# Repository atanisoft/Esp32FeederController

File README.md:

# Esp32FeederController

The Esp32FeederController project allows controlling of multiple 0816 Feeders
using four wire cables.

## Supported Feeders

At this time the following feeder designs should work:

* [Original 0816 Feeder](https://docs.mgrl.de/maschine:pickandplace:feeder:0816feeder).
* [0816 Lumen Feeder](https://github.com/SupaCoder/0816-Lumen-SMT-Feeder-Remix).
* [Max Feeder](https://github.com/CurlyTaleGamesLLC/MAXFeederShield).

The [Max Feeder](https://github.com/CurlyTaleGamesLLC/MAXFeederShield) is the preferred
version of the feeder design as it supports adding a QR Code to the feeder that can be
used for automatic part identification.

### Feeder modifications / Addons

* [Reel holder](https://www.thingiverse.com/thing:3810696)
* [Vertical tape puller](https://github.com/SebG3D/TapePuller/wiki)

## Non-automatic feeders

* [Lumen Push/Pull Feeder](https://github.com/GatCode/LumenPPF)

# Adding Esp32FeederController to OpenPnP

Adding Esp32FeederController to OpenPnP consists of three steps:

* Create [GcodeDriver](https://github.com/openpnp/openpnp/wiki/GcodeDriver).
* Create [Actuators](https://github.com/openpnp/openpnp/wiki/Setup-and-Calibration%3A-Actuators) for Feeder actions.
* Create [Feeders](https://github.com/openpnp/openpnp/wiki/Setup-and-Calibration%3A-Feeders). 

### Creating the Gcode Driver

Each Esp32FeederController PCB should have it's own [GcodeDriver](https://github.com/openpnp/openpnp/wiki/GcodeDriver).

Steps to add a new [GcodeDriver](https://github.com/openpnp/openpnp/wiki/GcodeDriver) for Esp32FeederController:

* Navigate to the `Machine Setup` tab
* Traverse the list to the `Drivers` section, select and expand it.
* Click the `+` (add) icon and select `GcodeDriver`.
* Select the newly created `GcodeDriver GcodeDriver` entry.
* Set the `Name` so it can be easily identified later.
* Set `Communications Type` to `tcp`.
* Scroll down to the `TCP` section.
* Set `IP Address` based on the reported IP address in the serial output.
* Set `Port` to `8989`.
* Click the `Apply` button to save the updates.
* In the `File` menu select `Save Configuration` to ensure settings are not lost when restarting OpenPnP.

### Creating Actuators

Each Esp32FeederController PCB requires two `Actuators`:

* Feeder Advancement
* Feeder Post Pick

The following steps should be executed for the two `Actuators`:

* Navigate to the `Machine Setup` tab
* Traverse the list to the `Actuators` section, select and expand it.
* Click the `+` (add) icon and select `ReferenceActuator`.
* Select the newly created `ReferenceActuator ReferenceActuator` entry.
* Set `Driver` to the Esp32FeederController driver created previously.
* Set the `Name` so it can be easily identified later.
* Set `Value Type` to `Double`.
* Click the `Apply` button to save the updates.
* In the `File` menu select `Save Configuration` to ensure settings are not lost when restarting OpenPnP.

After the two `Actuators` have been defined it is necessary to configure the
Gcode commands to send for actuation, use the following steps to configure this:

* Navigate to the `Machine Setup` tab
* Traverse the list to the `Drivers` section, select and expand it.
* Click the `GcodeDriver Esp32FeederController` (or whatever name was provided previously).
* Navigate to the `Gcode` tab.
* In `Head Mountable` drop down select `Default`.
  * In `Setting` select `COMMAND_CONFIRM_REGEX` and enter `^ok.*`, be sure to click `Apply` before moving further.
  * In `Setting` select `COMMAND_ERROR_REGEX` and enter `^error.*`, be sure to click `Apply` before moving further.
* In `Head Mountable` drop down select `Actuator: [No Head] Feeder Advancement`.
  * In `Setting` select `ACTUATE_DOUBLE_COMMAND` and enter `M610 N{IntegerValue}*`, be sure to click `Apply` before moving further.
* In `Head Mountable` drop down select `Actuator: [No Head] Feeder Post Pick`.
  * In `Setting` select `ACTUATE_DOUBLE_COMMAND` and enter `M611 N{IntegerValue}*`, be sure to click `Apply` before moving further.
* In the `File` menu select `Save Configuration` to ensure settings are not lost when restarting OpenPnP.

## Configuring Feeders in OpenPnP

There are two types of feeders that will work well with Esp32FeederController:

* [ReferenceAutoFeeder](https://github.com/openpnp/openpnp/wiki/ReferenceAutoFeeder)
* [ReferenceSlotAutoFeeder](https://github.com/openpnp/openpnp/wiki/ReferenceSlotAutoFeeder)

Both operate similarly using the `Actuators` defined above.

* Navigate to the `Feeders` tab
* Click the `+` (add) icon and select `ReferenceAutoFeeder` or `ReferenceSlotAutoFeeder`.
* Select the newly created `ReferenceAutoFeeder ReferenceAutoFeeder` or `ReferenceSlotAutoFeeder ReferenceSlotAutoFeeder` entry.
* Double click on the newly created row in the `Name` column and rename it for easier identification.
* Set `Feed Actuator` to `Feeder Advancement` (or whichever name you provide the `Actuator`)
* Set `Post Pick Actuator` to `Feeder Post Pick` (or whichever name you provide the `Actuator`)
* Set `Actuator Value` on both `Actuators` to the feeder number on the Esp32FeederController PCB minus one (zero indexed).
* Click the `Apply` button to save the updates.
* In the `File` menu select `Save Configuration` to ensure settings are not lost when restarting OpenPnP.

Use the `Test Feed` and `Test post pick` to confirm the feeder is responding correctly.

## Supported Gcode commands

The Esp32FeederController supports multiple Gcode commands, many of which are
not directly used by OpenPnP. Many of the commands are intended to be used with
substitution of values within `{ }` marks, anything within `[ ]` are optional
arguments.

### Feeder Movement (M610)

`M610 N{feeder} [D{distance}]`

* `{feeder}` is the Feeder to be moved forward.
* `{distance}` is the distance to move the feeder and is optional.

### Feeder Post Pick (M611)

`M611 N{feeder}`

* `{feeder}` is the Feeder to be moved as part of post-pick.

### Feeder Status (M612)

`M612 N{feeder}`

* `{feeder}` is the Feeder to retrieve status for.

### Feeder Configuration (M613)

`M613 N{feeder} [A{advance angle}] [B{half advance angle}] [C{retract angle}] [D{degrees}] [F{feed length}] [S{speed}] [U{settle time}] [V{min pulse}] [W{max pulse}] [Z{feedback enabled}]`

All parameters except `{feeder}` are optional.

* `{feeder}` is the Feeder to be configured.
* `{advance angle}` is the angle to move the servo to for full extension.
* `{half advance angle}` is the angle to move the servo to for half extension.
* `{retract angle}` is the angle to move the servo to for retraction.
* `{degrees}` is the maximum number of degrees to move at one time, set to zero to move immediately.
* `{feed length}` is the number of millimeters (pitch) to move the feeder forward when moving to the next part and must be a multiple of 2.
* `{speed}` is the interval at which to move the servo between two angles, used in conjunction with `{degrees}`.
* `{settle time}` is the number of milliseconds to delay between servo movements.
* `{min pulse}` is the minimum number of pulses to send the servo.
* `{max pulse}` is the maximum number of pulses to send the servo.
* `{feedback enabled}` is used to enable or disable feedback checking as part of movement, set to zero to disable or one to enable

### Enable Feeder (M614)

`M614 N{feeder}`

* `{feeder}` is the Feeder to enable.

### Disable Feeder (M615)

`M615 N{feeder}`

* `{feeder}` is the Feeder to disable.

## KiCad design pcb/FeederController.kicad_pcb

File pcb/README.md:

# Custom PCBs

This tree contains custom PCBs for the Esp32FeederController. Note that this PCB
has not been extensively tested or verified to be bug-free. Please report any
issues with the PCBs and if possible a PR to correct them.

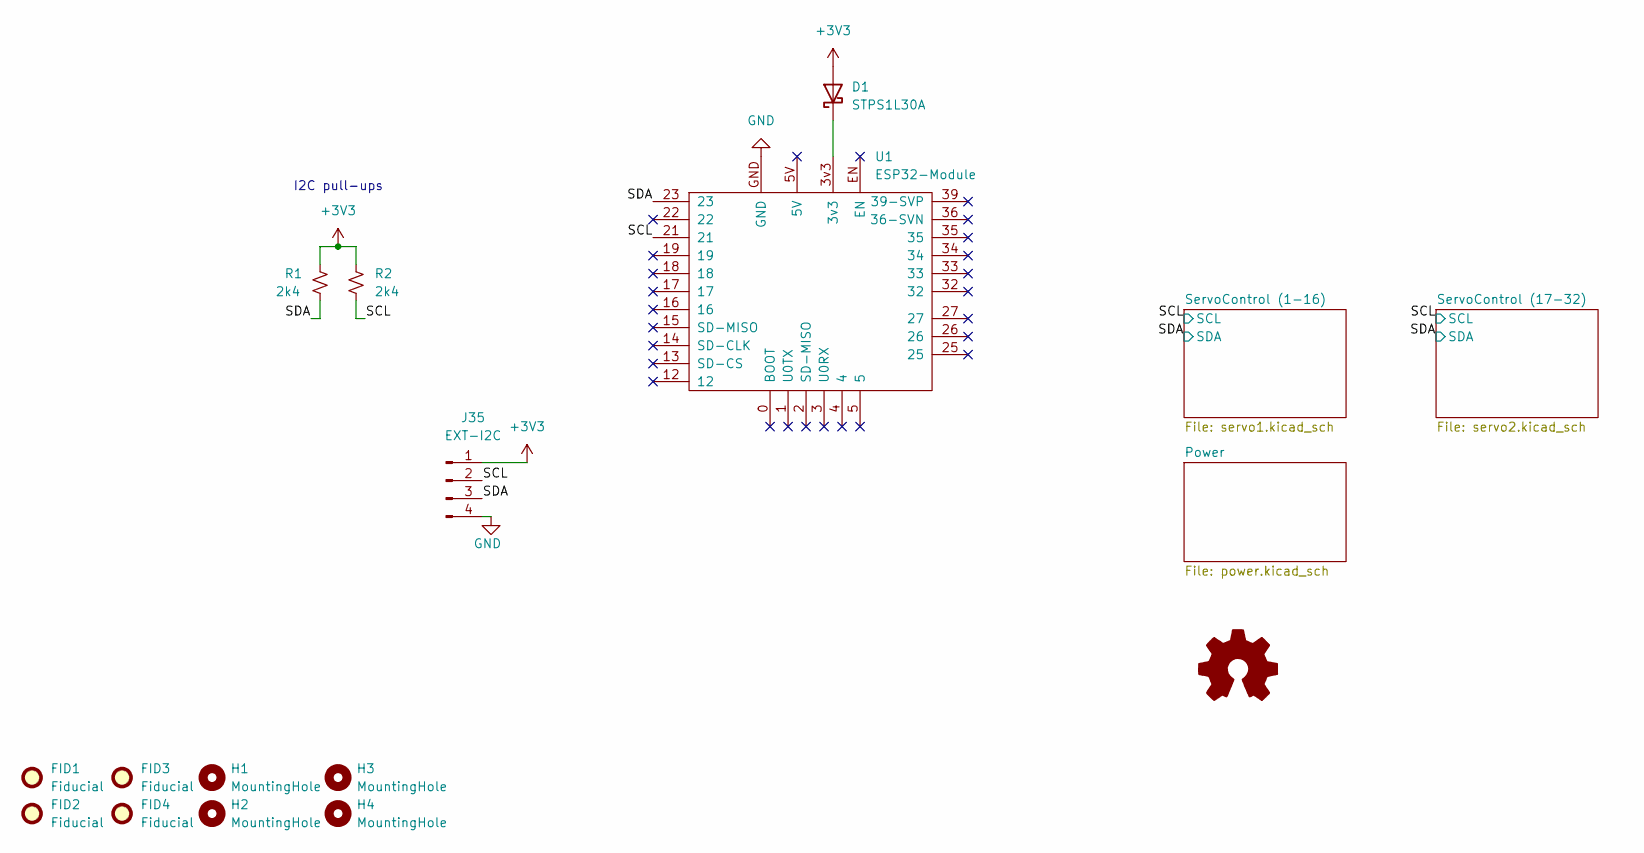
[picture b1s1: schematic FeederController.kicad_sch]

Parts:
D1: STPS1L30A; D_SMA_Handsoldering; Mouser 511-STPS1L30AFN
FID1, FID2, FID3, FID4: Fiducial; Fiducial_0.5mm_Mask1mm
H1, H2, H3, H4: MountingHole; MountingHole_3.2mm_M3_Pad
J35: EXT-I2C; PinHeader_1x04_P2.54mm_Vertical
R1, R2: 2k4; R_0603_1608Metric_Pad0.98x0.95mm_HandSolder
U1: ESP32-Module; TTGO-T1-DEVKIT-C

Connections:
+3V3: D1.2 (A), J35.1, R1.1, R2.1; also elsewhere on the board
/SCL: J35.2, R2.2, U1.21; also elsewhere on the board
/SDA: J35.3, R1.2, U1.23; also elsewhere on the board
GND: J35.4, U1.GND; also elsewhere on the board
unnamed: D1.1 (K), U1.3v3

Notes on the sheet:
I2C pull-ups

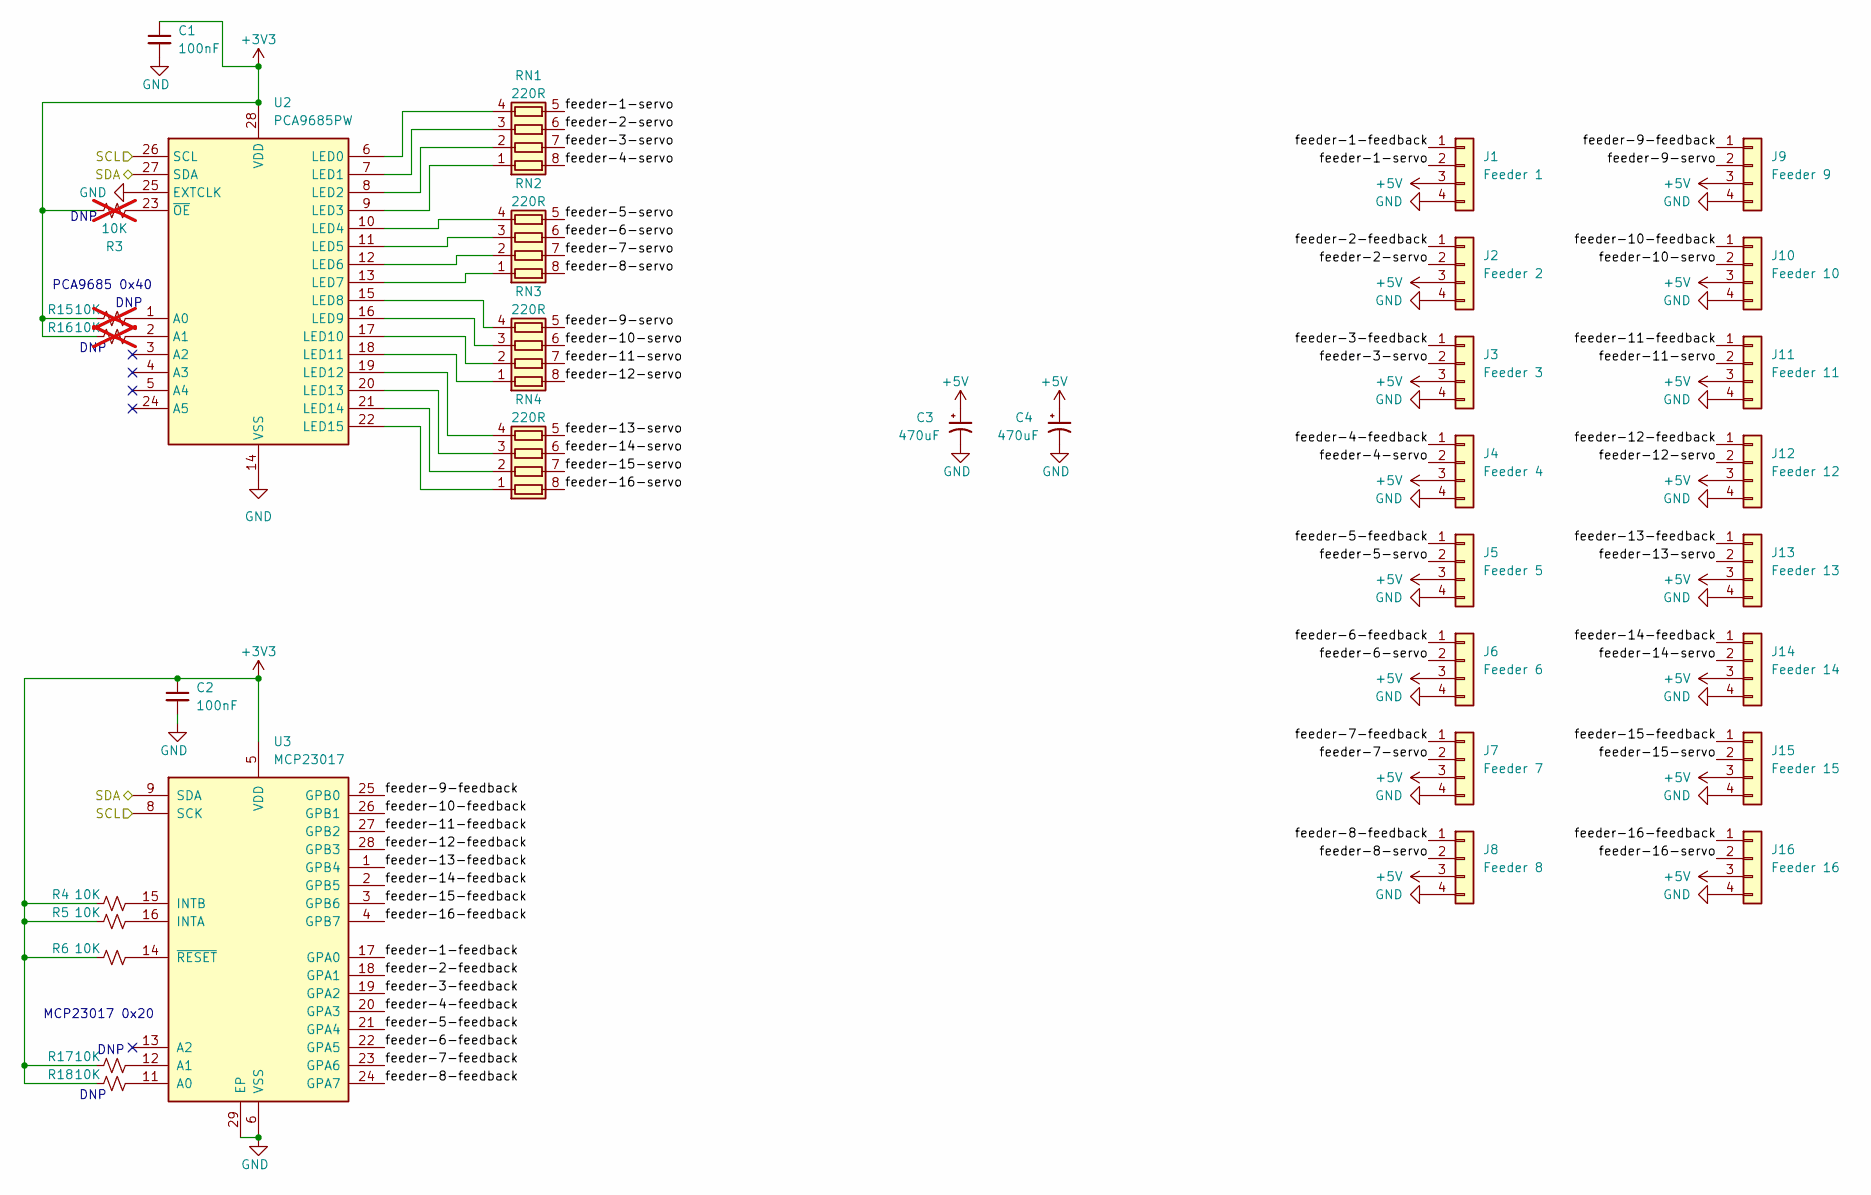
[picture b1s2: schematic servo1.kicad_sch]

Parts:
C1, C2: 100nF; C_0603_1608Metric_Pad1.08x0.95mm_HandSolder; Mouser 791-0603B822K250CT
C3, C4: 470uF; CP_Radial_D8.0mm_P5.00mm
J1: Feeder 1; PinHeader_1x04_P2.54mm_Vertical
J2: Feeder 2; PinHeader_1x04_P2.54mm_Vertical
J3: Feeder 3; PinHeader_1x04_P2.54mm_Vertical
J4: Feeder 4; PinHeader_1x04_P2.54mm_Vertical
J5: Feeder 5; PinHeader_1x04_P2.54mm_Vertical
J6: Feeder 6; PinHeader_1x04_P2.54mm_Vertical
J7: Feeder 7; PinHeader_1x04_P2.54mm_Vertical
J8: Feeder 8; PinHeader_1x04_P2.54mm_Vertical
J9: Feeder 9; PinHeader_1x04_P2.54mm_Vertical
J10: Feeder 10; PinHeader_1x04_P2.54mm_Vertical
J11: Feeder 11; PinHeader_1x04_P2.54mm_Vertical
J12: Feeder 12; PinHeader_1x04_P2.54mm_Vertical
J13: Feeder 13; PinHeader_1x04_P2.54mm_Vertical
J14: Feeder 14; PinHeader_1x04_P2.54mm_Vertical
J15: Feeder 15; PinHeader_1x04_P2.54mm_Vertical
J16: Feeder 16; PinHeader_1x04_P2.54mm_Vertical
R3, R15, R16: 10K; R_0603_1608Metric_Pad0.98x0.95mm_HandSolder; Mouser 279-CRGCQ0603F10K; not fitted
R4, R5, R6, R17, R18: 10K; R_0603_1608Metric_Pad0.98x0.95mm_HandSolder; Mouser 279-CRGCQ0603F10K
RN1, RN2, RN3, RN4: 220R; R_Array_Concave_4x0402
U2: PCA9685PW; TSSOP-28_4.4x9.7mm_P0.65mm
U3: MCP23017; QFN-28-1EP_6x6mm_P0.65mm_EP4.25x4.25mm

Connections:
+3V3: C1.1, C2.1, R3.1, R4.1, R5.1, R6.1, R15.1, R16.1, R17.1, R18.1, U2.28 (VDD), U3.5 (VDD); also elsewhere on the board
+5V: C3.1, C4.1, J1.3, J2.3, J3.3, J4.3, J5.3, J6.3, J7.3, J8.3, J9.3, J10.3, J11.3, J12.3, J13.3, J14.3, J15.3, J16.3; also elsewhere on the board
/SCL: U2.26 (SCL), U3.8 (SCK); also elsewhere on the board
/SDA: U2.27 (SDA), U3.9 (SDA); also elsewhere on the board
/ServoControl (1-16)/feeder-1-feedback: J1.1, U3.17 (GPA0)
/ServoControl (1-16)/feeder-1-servo: J1.2, RN1.5 (R4.2)
/ServoControl (1-16)/feeder-2-feedback: J2.1, U3.18 (GPA1)
/ServoControl (1-16)/feeder-2-servo: J2.2, RN1.6 (R3.2)
/ServoControl (1-16)/feeder-3-feedback: J3.1, U3.19 (GPA2)
/ServoControl (1-16)/feeder-3-servo: J3.2, RN1.7 (R2.2)
/ServoControl (1-16)/feeder-4-feedback: J4.1, U3.20 (GPA3)
/ServoControl (1-16)/feeder-4-servo: J4.2, RN1.8 (R1.2)
/ServoControl (1-16)/feeder-5-feedback: J5.1, U3.21 (GPA4)
/ServoControl (1-16)/feeder-5-servo: J5.2, RN2.5 (R4.2)
/ServoControl (1-16)/feeder-6-feedback: J6.1, U3.22 (GPA5)
/ServoControl (1-16)/feeder-6-servo: J6.2, RN2.6 (R3.2)
/ServoControl (1-16)/feeder-7-feedback: J7.1, U3.23 (GPA6)
/ServoControl (1-16)/feeder-7-servo: J7.2, RN2.7 (R2.2)
/ServoControl (1-16)/feeder-8-feedback: J8.1, U3.24 (GPA7)
/ServoControl (1-16)/feeder-8-servo: J8.2, RN2.8 (R1.2)
/ServoControl (1-16)/feeder-9-feedback: J9.1, U3.25 (GPB0)
/ServoControl (1-16)/feeder-9-servo: J9.2, RN3.5 (R4.2)
/ServoControl (1-16)/feeder-10-feedback: J10.1, U3.26 (GPB1)
/ServoControl (1-16)/feeder-10-servo: J10.2, RN3.6 (R3.2)
/ServoControl (1-16)/feeder-11-feedback: J11.1, U3.27 (GPB2)
/ServoControl (1-16)/feeder-11-servo: J11.2, RN3.7 (R2.2)
/ServoControl (1-16)/feeder-12-feedback: J12.1, U3.28 (GPB3)
/ServoControl (1-16)/feeder-12-servo: J12.2, RN3.8 (R1.2)
/ServoControl (1-16)/feeder-13-feedback: J13.1, U3.1 (GPB4)
/ServoControl (1-16)/feeder-13-servo: J13.2, RN4.5 (R4.2)
/ServoControl (1-16)/feeder-14-feedback: J14.1, U3.2 (GPB5)
/ServoControl (1-16)/feeder-14-servo: J14.2, RN4.6 (R3.2)
/ServoControl (1-16)/feeder-15-feedback: J15.1, U3.3 (GPB6)
/ServoControl (1-16)/feeder-15-servo: J15.2, RN4.7 (R2.2)
/ServoControl (1-16)/feeder-16-feedback: J16.1, U3.4 (GPB7)
/ServoControl (1-16)/feeder-16-servo: J16.2, RN4.8 (R1.2)
GND: C1.2, C2.2, C3.2, C4.2, J1.4, J2.4, J3.4, J4.4, J5.4, J6.4, J7.4, J8.4, J9.4, J10.4, J11.4, J12.4, J13.4, J14.4, J15.4, J16.4, U2.14 (VSS), U2.25 (EXTCLK), U3.6 (VSS), U3.29 (EP); also elsewhere on the board
unnamed: R4.2, U3.15 (INTB)
unnamed: R5.2, U3.16 (INTA)
unnamed: R6.2, U3.14 (~RESET)
unnamed: RN1.1 (R1.1), U2.9 (LED3)
unnamed: RN1.2 (R2.1), U2.8 (LED2)
unnamed: RN1.3 (R3.1), U2.7 (LED1)
unnamed: RN1.4 (R4.1), U2.6 (LED0)
unnamed: RN2.1 (R1.1), U2.13 (LED7)
unnamed: RN2.2 (R2.1), U2.12 (LED6)
unnamed: RN2.3 (R3.1), U2.11 (LED5)
unnamed: RN2.4 (R4.1), U2.10 (LED4)
unnamed: RN3.1 (R1.1), U2.18 (LED11)
unnamed: RN3.2 (R2.1), U2.17 (LED10)
unnamed: RN3.3 (R3.1), U2.16 (LED9)
unnamed: RN3.4 (R4.1), U2.15 (LED8)
unnamed: RN4.1 (R1.1), U2.22 (LED15)
unnamed: RN4.2 (R2.1), U2.21 (LED14)
unnamed: RN4.3 (R3.1), U2.20 (LED13)
unnamed: RN4.4 (R4.1), U2.19 (LED12)
unnamed: R15.2, U2.1 (A0)
unnamed: R16.2, U2.2 (A1)
unnamed: R3.2, U2.23 (~OE)
unnamed: R18.2, U3.11 (A0)
unnamed: R17.2, U3.12 (A1)

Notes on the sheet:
DNP
MCP23017 0x20
PCA9685 0x40

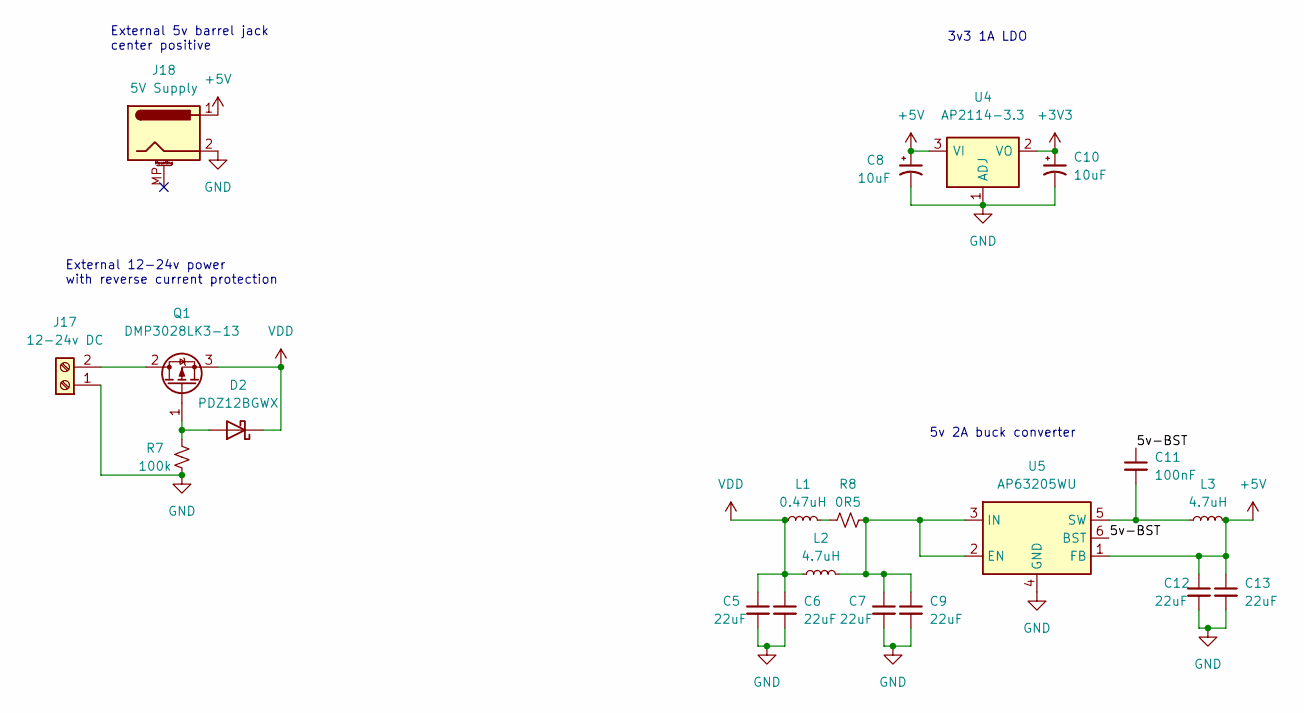
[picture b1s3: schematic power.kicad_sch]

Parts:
C5, C6, C9, C12, C13: 22uF; C_0603_1608Metric_Pad1.08x0.95mm_HandSolder; Mouser 810-C1608X5R0J226M
C7: 22uF; C_0603_1608Metric_Pad1.08x0.95mm_HandSolder; Mouser 810-C1608X5R0J226
C8, C10: 10uF; CP_Elec_5x5.3; Mouser 710-865230542002
C11: 100nF; C_0603_1608Metric_Pad1.08x0.95mm_HandSolder; Mouser 603-CC603KPX7R9BB104
D2: PDZ12BGWX; D_SOD-123; Mouser 771-PDZ12BGWX
J17: 12-24v DC; TerminalBlock_Phoenix_MKDS-1,5-2-5.08_1x02_P5.08mm_Horizont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; Mouser 649-220316-H021B01LF
J18: 5V Supply; BarrelJack_Horizontal
L1: 0.47uH; L_0603_1608Metric_Pad1.05x0.95mm_HandSolder; Mouser 810-MLZ1608DR47DT000
L2, L3: 4.7uH; L_Taiyo-Yuden_NR-40xx_HandSoldering; Mouser 963-NRS4018T4R7MDGJ
Q1: DMP3028LK3-13; TO-252-2; Mouser 621-DMP3028LK3-13
R7: 100k; R_1206_3216Metric_Pad1.30x1.75mm_HandSolder; Mouser 71-CRCW1206100KFKEAC
R8: 0R5; R_0805_2012Metric_Pad1.20x1.40mm_HandSolder; Mouser 756-LRCS0805-R50FT5
U4: AP2114-3.3; SOT-223-3_TabPin2; Mouser 621-AP2114H-3.3TRG1
U5: AP63205WU; TSOT-23-6; Mouser 621-AP63205WU-7

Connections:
+3V3: C10.1, U4.2 (VO); also elsewhere on the board
+5V: C8.1, C12.1, C13.1, J18.1, L3.2, U4.3 (VI), U5.1 (FB); also elsewhere on the board
/Power/5v-BST: C11.1, U5.6 (BST)
GND: C5.2, C6.2, C7.2, C8.2, C9.2, C10.2, C12.2, C13.2, J17.1, J18.2, R7.1, U4.1 (ADJ), U5.4 (GND); also elsewhere on the board
unnamed: C7.1, C9.1, L2.2, R8.2, U5.2 (EN), U5.3 (IN)
unnamed: C11.2, L3.1, U5.5 (SW)
unnamed: D2.2 (A), Q1.1 (G), R7.2
unnamed: J17.2, Q1.2 (D)
unnamed: L1.2, R8.1
VDD: C5.1, C6.1, D2.1 (K), L1.1, L2.1, Q1.3 (S)

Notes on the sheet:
5v 2A buck converter
External 12-24v power with reverse current protection
3v3 1A LDO
External 5v barrel jack center positive

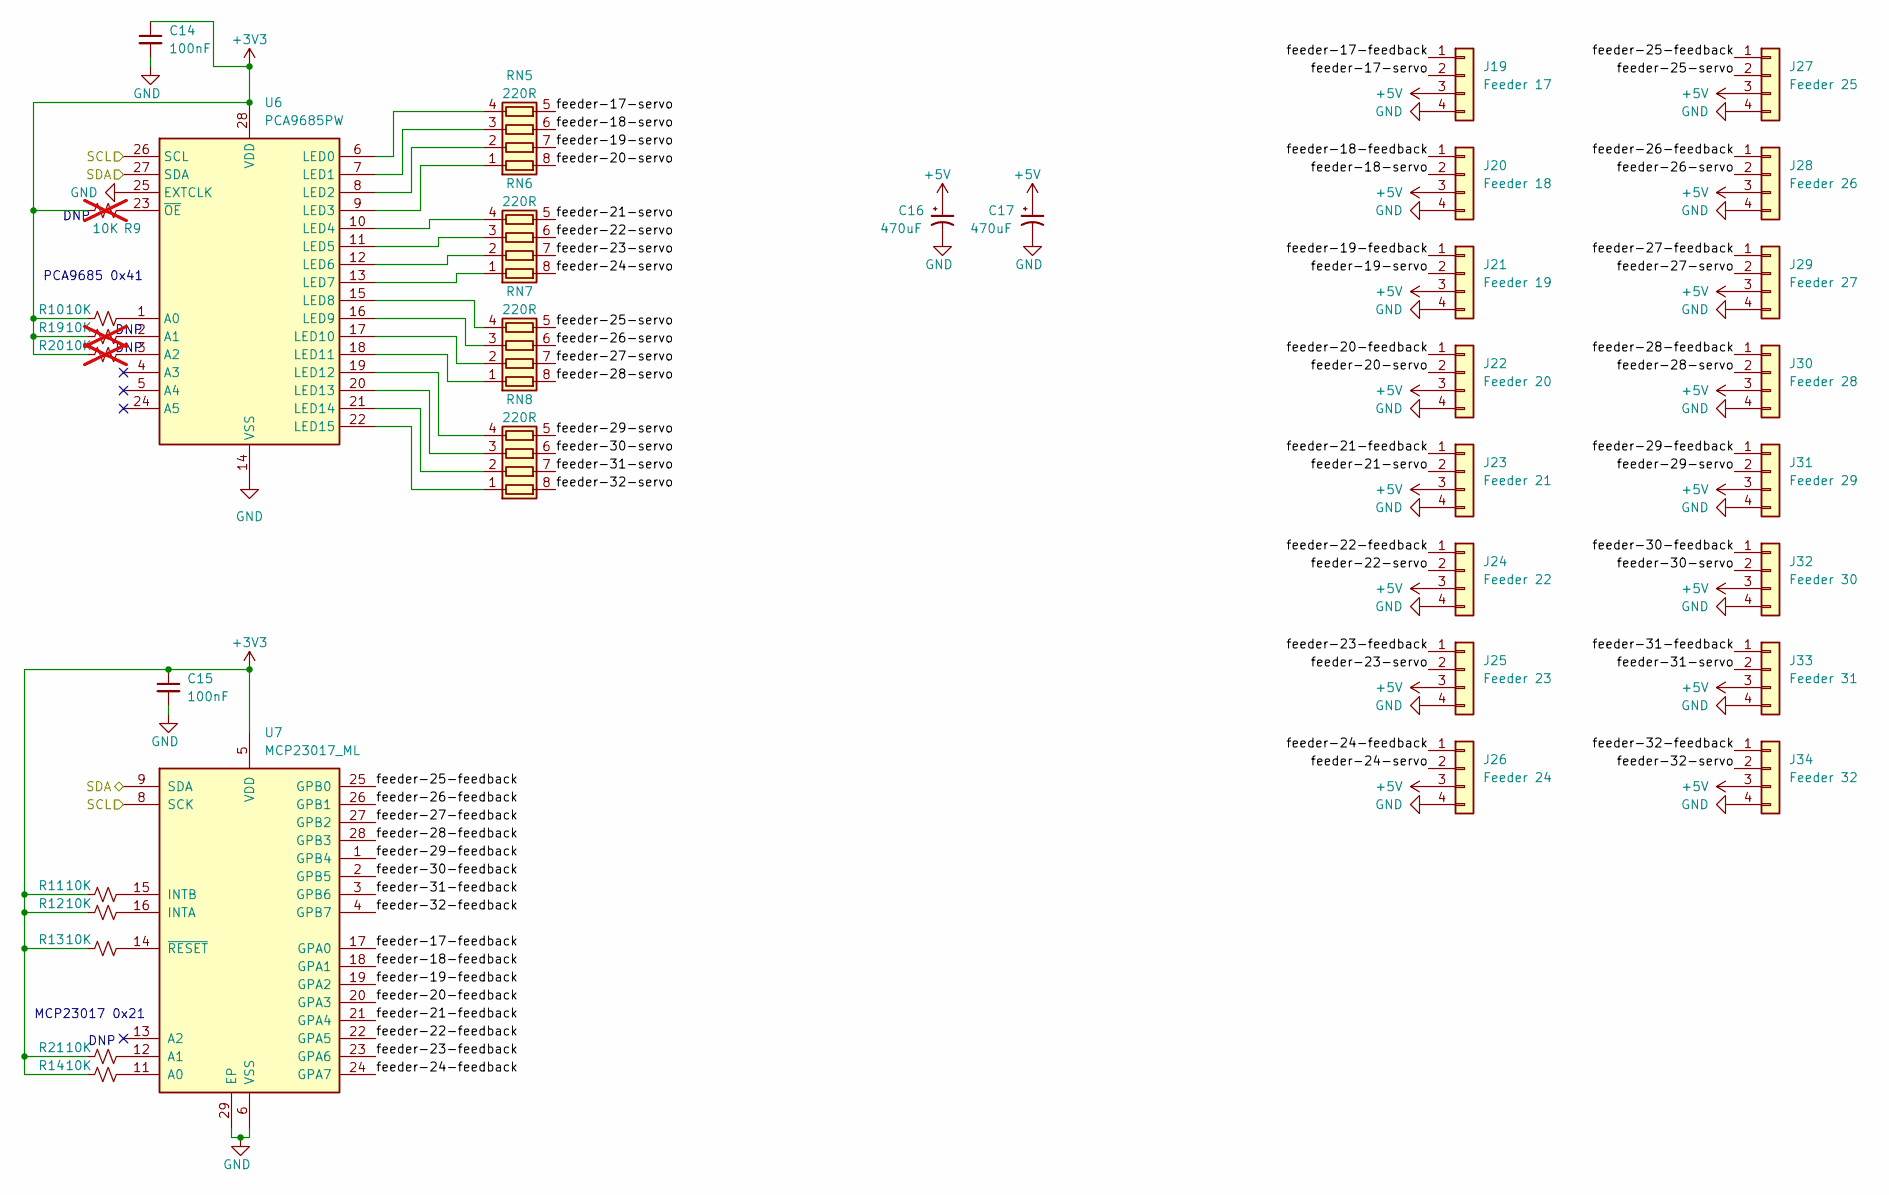
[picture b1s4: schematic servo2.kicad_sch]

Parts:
C14: 100nF; C_0603_1608Metric_Pad1.08x0.95mm_HandSolder
C15: 100nF; C_0603_1608Metric_Pad1.08x0.95mm_HandSolder; Mouser 791-0603B822K250CT
C16, C17: 470uF; CP_Radial_D8.0mm_P5.00mm
J19: Feeder 17; PinHeader_1x04_P2.54mm_Vertical
J20: Feeder 18; PinHeader_1x04_P2.54mm_Vertical
J21: Feeder 19; PinHeader_1x04_P2.54mm_Vertical
J22: Feeder 20; PinHeader_1x04_P2.54mm_Vertical
J23: Feeder 21; PinHeader_1x04_P2.54mm_Vertical
J24: Feeder 22; PinHeader_1x04_P2.54mm_Vertical
J25: Feeder 23; PinHeader_1x04_P2.54mm_Vertical
J26: Feeder 24; PinHeader_1x04_P2.54mm_Vertical
J27: Feeder 25; PinHeader_1x04_P2.54mm_Vertical
J28: Feeder 26; PinHeader_1x04_P2.54mm_Vertical
J29: Feeder 27; PinHeader_1x04_P2.54mm_Vertical
J30: Feeder 28; PinHeader_1x04_P2.54mm_Vertical
J31: Feeder 29; PinHeader_1x04_P2.54mm_Vertical
J32: Feeder 30; PinHeader_1x04_P2.54mm_Vertical
J33: Feeder 31; PinHeader_1x04_P2.54mm_Vertical
J34: Feeder 32; PinHeader_1x04_P2.54mm_Vertical
R9, R19, R20: 10K; R_0603_1608Metric_Pad0.98x0.95mm_HandSolder; Mouser 279-CRGCQ0603F10K; not fitted
R10, R11, R12, R13, R14, R21: 10K; R_0603_1608Metric_Pad0.98x0.95mm_HandSolder; Mouser 279-CRGCQ0603F10K
RN5, RN6, RN7, RN8: 220R; R_Array_Concave_4x0402
U6: PCA9685PW; TSSOP-28_4.4x9.7mm_P0.65mm
U7: MCP23017_ML; QFN-28-1EP_6x6mm_P0.65mm_EP4.25x4.25mm

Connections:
+3V3: C14.1, C15.1, R9.1, R10.1, R11.1, R12.1, R13.1, R14.1, R19.1, R20.1, R21.1, U6.28 (VDD), U7.5 (VDD); also elsewhere on the board
+5V: C16.1, C17.1, J19.3, J20.3, J21.3, J22.3, J23.3, J24.3, J25.3, J26.3, J27.3, J28.3, J29.3, J30.3, J31.3, J32.3, J33.3, J34.3; also elsewhere on the board
/SCL: U6.26 (SCL), U7.8 (SCK); also elsewhere on the board
/SDA: U6.27 (SDA), U7.9 (SDA); also elsewhere on the board
/ServoControl (17-32)/feeder-17-feedback: J19.1, U7.17 (GPA0)
/ServoControl (17-32)/feeder-17-servo: J19.2, RN5.5 (R4.2)
/ServoControl (17-32)/feeder-18-feedback: J20.1, U7.18 (GPA1)
/ServoControl (17-32)/feeder-18-servo: J20.2, RN5.6 (R3.2)
/ServoControl (17-32)/feeder-19-feedback: J21.1, U7.19 (GPA2)
/ServoControl (17-32)/feeder-19-servo: J21.2, RN5.7 (R2.2)
/ServoControl (17-32)/feeder-20-feedback: J22.1, U7.20 (GPA3)
/ServoControl (17-32)/feeder-20-servo: J22.2, RN5.8 (R1.2)
/ServoControl (17-32)/feeder-21-feedback: J23.1, U7.21 (GPA4)
/ServoControl (17-32)/feeder-21-servo: J23.2, RN6.5 (R4.2)
/ServoControl (17-32)/feeder-22-feedback: J24.1, U7.22 (GPA5)
/ServoControl (17-32)/feeder-22-servo: J24.2, RN6.6 (R3.2)
/ServoControl (17-32)/feeder-23-feedback: J25.1, U7.23 (GPA6)
/ServoControl (17-32)/feeder-23-servo: J25.2, RN6.7 (R2.2)
/ServoControl (17-32)/feeder-24-feedback: J26.1, U7.24 (GPA7)
/ServoControl (17-32)/feeder-24-servo: J26.2, RN6.8 (R1.2)
/ServoControl (17-32)/feeder-25-feedback: J27.1, U7.25 (GPB0)
/ServoControl (17-32)/feeder-25-servo: J27.2, RN7.5 (R4.2)
/ServoControl (17-32)/feeder-26-feedback: J28.1, U7.26 (GPB1)
/ServoControl (17-32)/feeder-26-servo: J28.2, RN7.6 (R3.2)
/ServoControl (17-32)/feeder-27-feedback: J29.1, U7.27 (GPB2)
/ServoControl (17-32)/feeder-27-servo: J29.2, RN7.7 (R2.2)
/ServoControl (17-32)/feeder-28-feedback: J30.1, U7.28 (GPB3)
/ServoControl (17-32)/feeder-28-servo: J30.2, RN7.8 (R1.2)
/ServoControl (17-32)/feeder-29-feedback: J31.1, U7.1 (GPB4)
/ServoControl (17-32)/feeder-29-servo: J31.2, RN8.5 (R4.2)
/ServoControl (17-32)/feeder-30-feedback: J32.1, U7.2 (GPB5)
/ServoControl (17-32)/feeder-30-servo: J32.2, RN8.6 (R3.2)
/ServoControl (17-32)/feeder-31-feedback: J33.1, U7.3 (GPB6)
/ServoControl (17-32)/feeder-31-servo: J33.2, RN8.7 (R2.2)
/ServoControl (17-32)/feeder-32-feedback: J34.1, U7.4 (GPB7)
/ServoControl (17-32)/feeder-32-servo: J34.2, RN8.8 (R1.2)
GND: C14.2, C15.2, C16.2, C17.2, J19.4, J20.4, J21.4, J22.4, J23.4, J24.4, J25.4, J26.4, J27.4, J28.4, J29.4, J30.4, J31.4, J32.4, J33.4, J34.4, U6.14 (VSS), U6.25 (EXTCLK), U7.6 (VSS), U7.29 (EP); also elsewhere on the board
unnamed: R9.2, U6.23 (~OE)
unnamed: R10.2, U6.1 (A0)
unnamed: R11.2, U7.15 (INTB)
unnamed: R12.2, U7.16 (INTA)
unnamed: R13.2, U7.14 (~RESET)
unnamed: R14.2, U7.11 (A0)
unnamed: RN5.1 (R1.1), U6.9 (LED3)
unnamed: RN5.2 (R2.1), U6.8 (LED2)
unnamed: RN5.3 (R3.1), U6.7 (LED1)
unnamed: RN5.4 (R4.1), U6.6 (LED0)
unnamed: RN6.1 (R1.1), U6.13 (LED7)
unnamed: RN6.2 (R2.1), U6.12 (LED6)
unnamed: RN6.3 (R3.1), U6.11 (LED5)
unnamed: RN6.4 (R4.1), U6.10 (LED4)
unnamed: RN7.1 (R1.1), U6.18 (LED11)
unnamed: RN7.2 (R2.1), U6.17 (LED10)
unnamed: RN7.3 (R3.1), U6.16 (LED9)
unnamed: RN7.4 (R4.1), U6.15 (LED8)
unnamed: RN8.1 (R1.1), U6.22 (LED15)
unnamed: RN8.2 (R2.1), U6.21 (LED14)
unnamed: RN8.3 (R3.1), U6.20 (LED13)
unnamed: RN8.4 (R4.1), U6.19 (LED12)
unnamed: R19.2, U6.2 (A1)
unnamed: R20.2, U6.3 (A2)
unnamed: R21.2, U7.12 (A1)

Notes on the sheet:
DNP
MCP23017 0x21
PCA9685 0x41

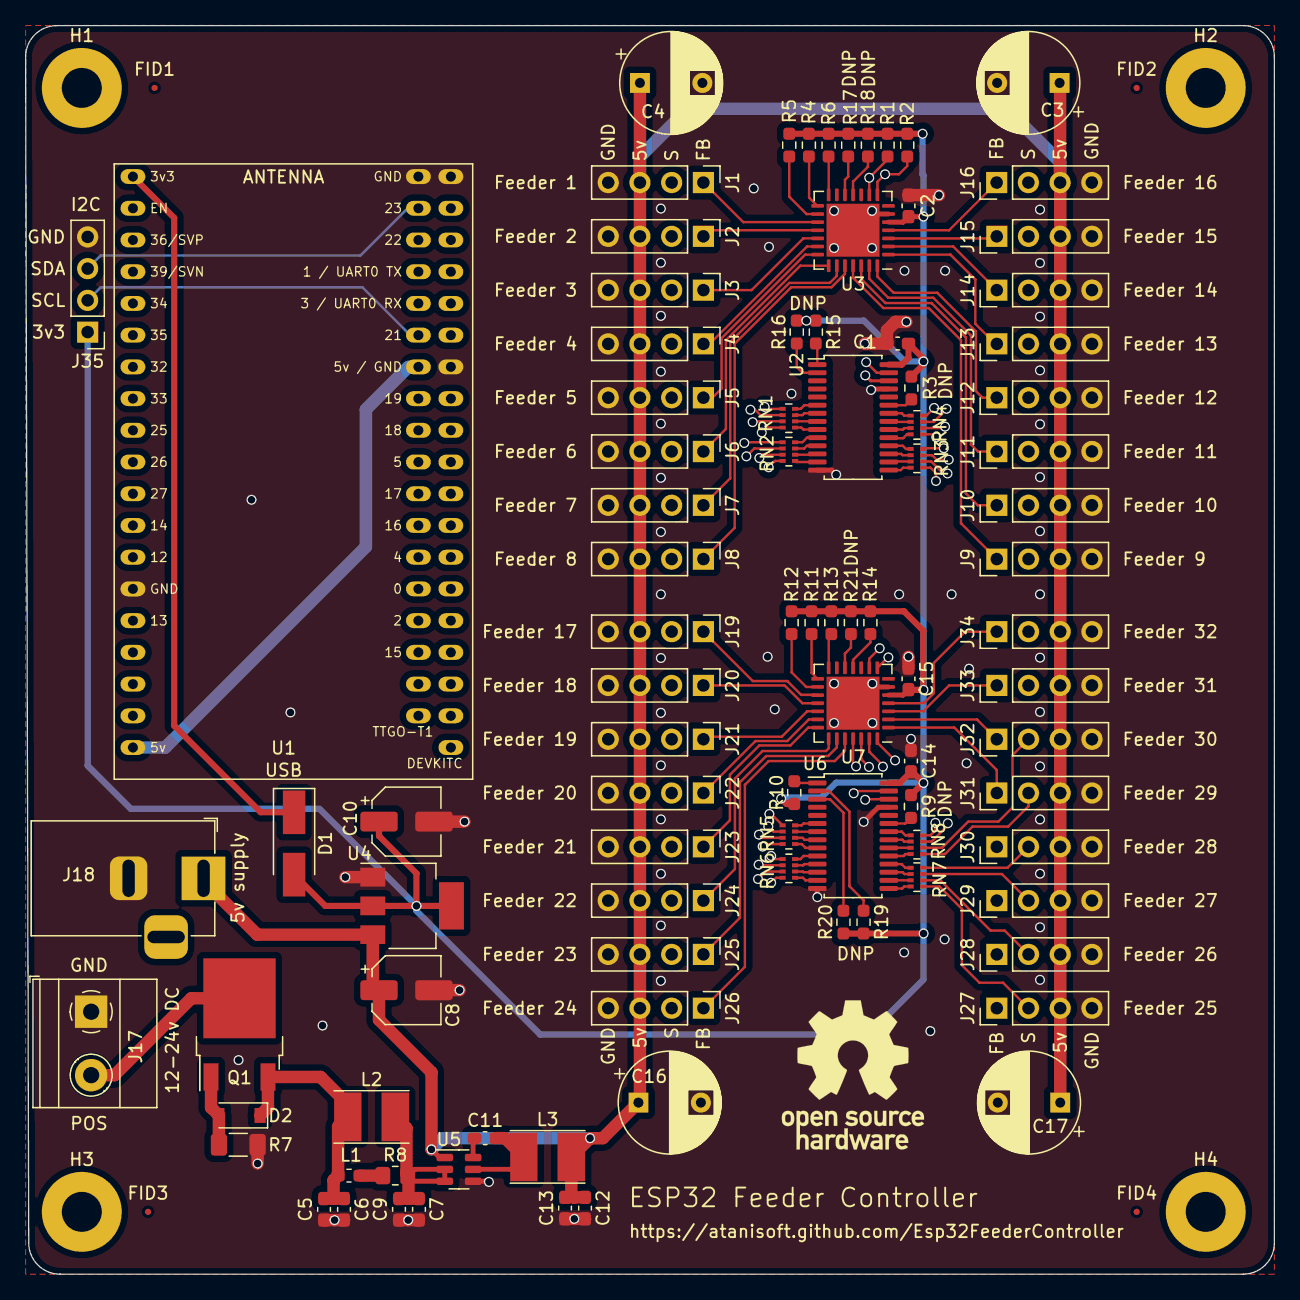
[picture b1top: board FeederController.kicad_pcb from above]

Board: 4 copper layers, 100.0 x 100.0 mm, 102 parts (0 on the bottom side), 126 nets.

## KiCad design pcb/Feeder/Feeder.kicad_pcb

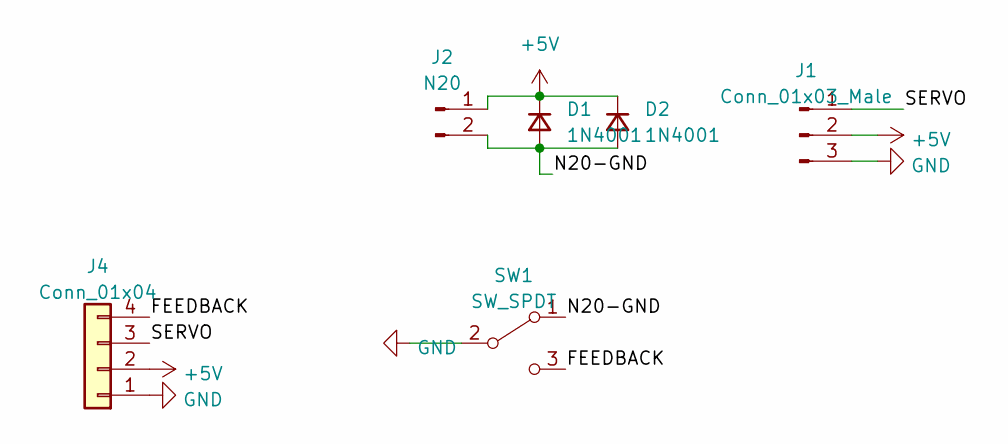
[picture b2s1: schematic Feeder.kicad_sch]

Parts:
D1: 1N4001; D_SMA-SMB_Universal_Handsoldering
D2: 1N4001; D_A-405_P7.62mm_Horizontal
J1: Conn_01x03_Male; PinSocket_1x03_P2.54mm_Vertical_Clean
J2: N20; PinSocket_1x02_P2.54mm_Vertical_Clean
J4: Conn_01x04; PinSocket_1x04_P2.54mm_Vertical_Clean
SW1: SW_SPDT; Microswitch

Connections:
+5V: D1.1 (K), D2.1 (K), J1.2, J2.1, J4.2
/FEEDBACK: J4.4, SW1.3 (C)
/N20-GND: D1.2 (A), D2.2 (A), J2.2, SW1.1 (A)
/SERVO: J1.1, J4.3
GND: J1.3, J4.1, SW1.2 (B)

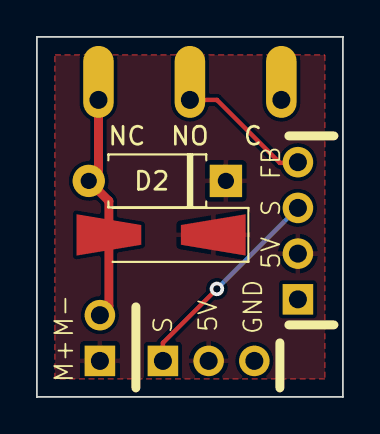
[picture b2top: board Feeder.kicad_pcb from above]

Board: 2 copper layers, 17.0 x 20.0 mm, 6 parts (0 on the bottom side), 5 nets.

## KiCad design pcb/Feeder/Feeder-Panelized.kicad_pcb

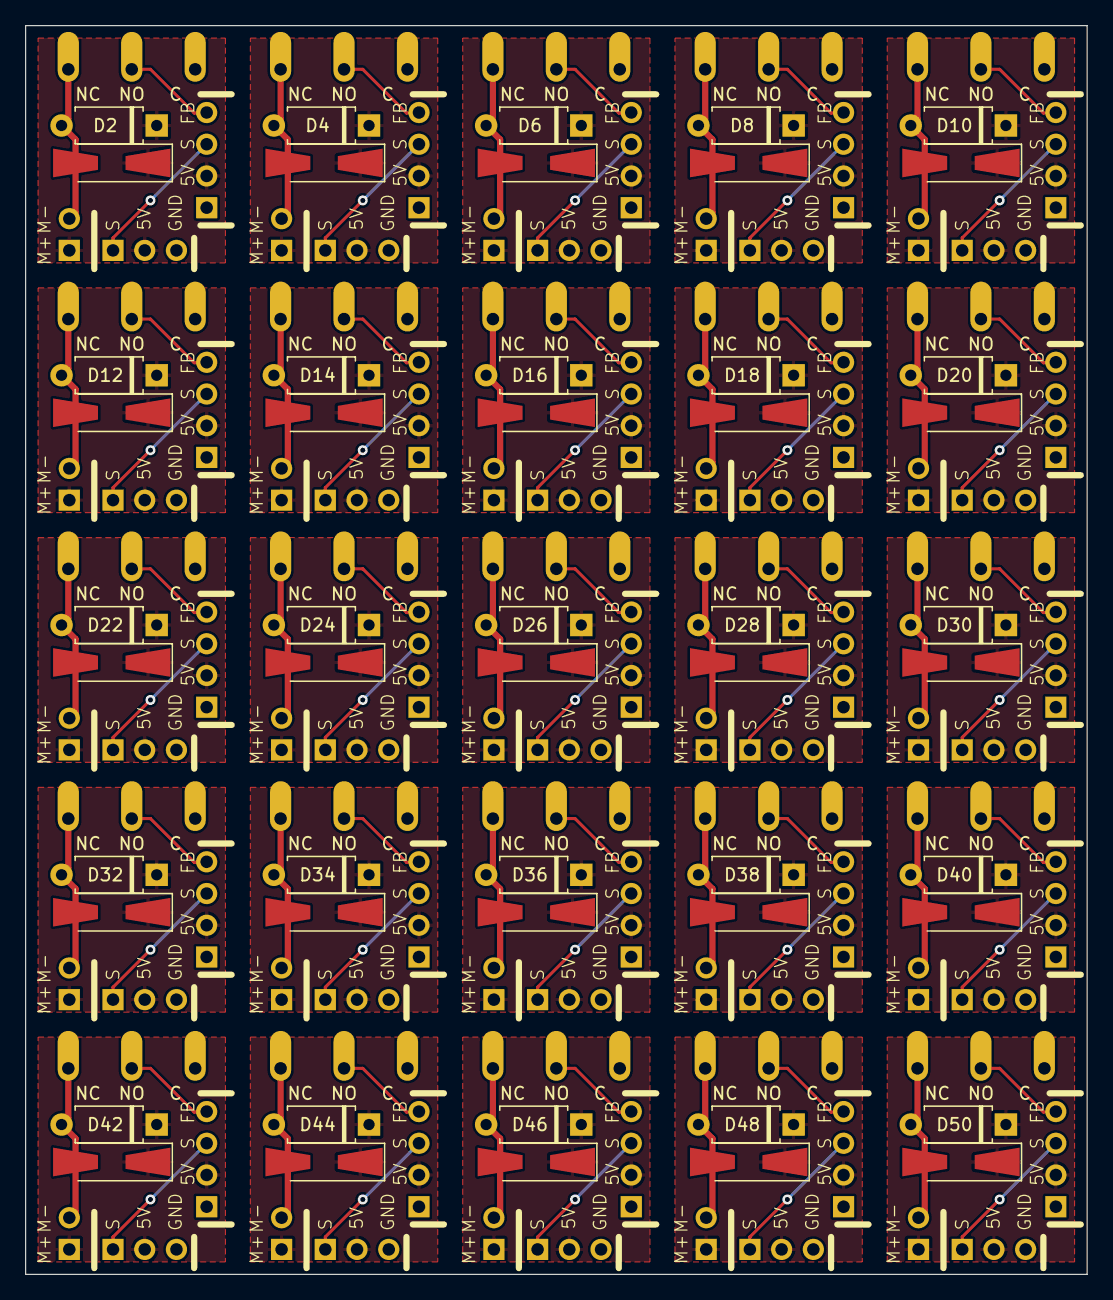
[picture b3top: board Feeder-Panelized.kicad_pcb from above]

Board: 2 copper layers, 85.0 x 100.0 mm, 150 parts (0 on the bottom side), 5 nets.

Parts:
D1, D3, D5, D7, D9, D11, D13, D15, D17, D19, D21, D23, D25, D27, D29, D31, D33, D35, D37, D39, D41, D43, D45, D47, D49: 1N4001; D_SMA-SMB_Universal_Handsoldering
D2, D4, D6, D8, D10, D12, D14, D16, D18, D20, D22, D24, D26, D28, D30, D32, D34, D36, D38, D40, D42, D44, D46, D48, D50: 1N4001; D_A-405_P7.62mm_Horizontal
J1, J3, J7, J10, J13, J16, J19, J22, J25, J28, J31, J34, J37, J40, J43, J46, J49, J52, J55, J58, J61, J64, J67, J70, J73: Conn_01x03_Male; PinSocket_1x03_P2.54mm_Vertical_Clean
J2, J5, J8, J11, J14, J17, J20, J23, J26, J29, J32, J35, J38, J41, J44, J47, J50, J53, J56, J59, J62, J65, J68, J71, J74: N20; PinSocket_1x02_P2.54mm_Vertical_Clean
J4, J6, J9, J12, J15, J18, J21, J24, J27, J30, J33, J36, J39, J42, J45, J48, J51, J54, J57, J60, J63, J66, J69, J72, J75: Conn_01x04; PinSocket_1x04_P2.54mm_Vertical_Clean
SW1, SW2, SW3, SW4, SW5, SW6, SW7, SW8, SW9, SW10, SW11, SW12, SW13, SW14, SW15, SW16, SW17, SW18, SW19, SW20, SW21, SW22, SW23, SW24, SW25: SW_SPDT; Microswitch

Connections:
+5V: D1.1 (K), D2.1 (K), D3.1 (K), D4.1 (K), D5.1 (K), D6.1 (K), D7.1 (K), D8.1 (K), D9.1 (K), D10.1 (K), D11.1 (K), D12.1 (K), D13.1 (K), D14.1 (K), D15.1 (K), D16.1 (K), D17.1 (K), D18.1 (K), D19.1 (K), D20.1 (K), D21.1 (K), D22.1 (K), D23.1 (K), D24.1 (K), D25.1 (K), D26.1 (K), D27.1 (K), D28.1 (K), D29.1 (K), D30.1 (K), D31.1 (K), D32.1 (K), D33.1 (K), D34.1 (K), D35.1 (K), D36.1 (K), D37.1 (K), D38.1 (K), D39.1 (K), D40.1 (K), D41.1 (K), D42.1 (K), D43.1 (K), D44.1 (K), D45.1 (K), D46.1 (K), D47.1 (K), D48.1 (K), D49.1 (K), D50.1 (K), J1.2, J2.1, J3.2, J4.2, J5.1, J6.2, J7.2, J8.1, J9.2, J10.2, J11.1, J12.2, J13.2, J14.1, J15.2, J16.2, J17.1, J18.2, J19.2, J20.1, J21.2, J22.2, J23.1, J24.2, J25.2, J26.1, J27.2, J28.2, J29.1, J30.2, J31.2, J32.1, J33.2, J34.2, J35.1, J36.2, J37.2, J38.1, J39.2, J40.2, J41.1, J42.2, J43.2, J44.1, J45.2, J46.2, J47.1, J48.2, J49.2, J50.1, J51.2, J52.2, J53.1, J54.2, J55.2, J56.1, J57.2, J58.2, J59.1, J60.2, J61.2, J62.1, J63.2, J64.2, J65.1, J66.2, J67.2, J68.1, J69.2, J70.2, J71.1, J72.2, J73.2, J74.1, J75.2
/FEEDBACK: J4.4, J6.4, J9.4, J12.4, J15.4, J18.4, J21.4, J24.4, J27.4, J30.4, J33.4, J36.4, J39.4, J42.4, J45.4, J48.4, J51.4, J54.4, J57.4, J60.4, J63.4, J66.4, J69.4, J72.4, J75.4, SW1.3 (C), SW2.3 (C), SW3.3 (C), SW4.3 (C), SW5.3 (C), SW6.3 (C), SW7.3 (C), SW8.3 (C), SW9.3 (C), SW10.3 (C), SW11.3 (C), SW12.3 (C), SW13.3 (C), SW14.3 (C), SW15.3 (C), SW16.3 (C), SW17.3 (C), SW18.3 (C), SW19.3 (C), SW20.3 (C), SW21.3 (C), SW22.3 (C), SW23.3 (C), SW24.3 (C), SW25.3 (C)
/N20-GND: D1.2 (A), D2.2 (A), D3.2 (A), D4.2 (A), D5.2 (A), D6.2 (A), D7.2 (A), D8.2 (A), D9.2 (A), D10.2 (A), D11.2 (A), D12.2 (A), D13.2 (A), D14.2 (A), D15.2 (A), D16.2 (A), D17.2 (A), D18.2 (A), D19.2 (A), D20.2 (A), D21.2 (A), D22.2 (A), D23.2 (A), D24.2 (A), D25.2 (A), D26.2 (A), D27.2 (A), D28.2 (A), D29.2 (A), D30.2 (A), D31.2 (A), D32.2 (A), D33.2 (A), D34.2 (A), D35.2 (A), D36.2 (A), D37.2 (A), D38.2 (A), D39.2 (A), D40.2 (A), D41.2 (A), D42.2 (A), D43.2 (A), D44.2 (A), D45.2 (A), D46.2 (A), D47.2 (A), D48.2 (A), D49.2 (A), D50.2 (A), J2.2, J5.2, J8.2, J11.2, J14.2, J17.2, J20.2, J23.2, J26.2, J29.2, J32.2, J35.2, J38.2, J41.2, J44.2, J47.2, J50.2, J53.2, J56.2, J59.2, J62.2, J65.2, J68.2, J71.2, J74.2, SW1.1 (A), SW2.1 (A), SW3.1 (A), SW4.1 (A), SW5.1 (A), SW6.1 (A), SW7.1 (A), SW8.1 (A), SW9.1 (A), SW10.1 (A), SW11.1 (A), SW12.1 (A), SW13.1 (A), SW14.1 (A), SW15.1 (A), SW16.1 (A), SW17.1 (A), SW18.1 (A), SW19.1 (A), SW20.1 (A), SW21.1 (A), SW22.1 (A), SW23.1 (A), SW24.1 (A), SW25.1 (A)
/SERVO: J1.1, J3.1, J4.3, J6.3, J7.1, J9.3, J10.1, J12.3, J13.1, J15.3, J16.1, J18.3, J19.1, J21.3, J22.1, J24.3, J25.1, J27.3, J28.1, J30.3, J31.1, J33.3, J34.1, J36.3, J37.1, J39.3, J40.1, J42.3, J43.1, J45.3, J46.1, J48.3, J49.1, J51.3, J52.1, J54.3, J55.1, J57.3, J58.1, J60.3, J61.1, J63.3, J64.1, J66.3, J67.1, J69.3, J70.1, J72.3, J73.1, J75.3
GND: J1.3, J3.3, J4.1, J6.1, J7.3, J9.1, J10.3, J12.1, J13.3, J15.1, J16.3, J18.1, J19.3, J21.1, J22.3, J24.1, J25.3, J27.1, J28.3, J30.1, J31.3, J33.1, J34.3, J36.1, J37.3, J39.1, J40.3, J42.1, J43.3, J45.1, J46.3, J48.1, J49.3, J51.1, J52.3, J54.1, J55.3, J57.1, J58.3, J60.1, J61.3, J63.1, J64.3, J66.1, J67.3, J69.1, J70.3, J72.1, J73.3, J75.1, SW1.2 (B), SW2.2 (B), SW3.2 (B), SW4.2 (B), SW5.2 (B), SW6.2 (B), SW7.2 (B), SW8.2 (B), SW9.2 (B), SW10.2 (B), SW11.2 (B), SW12.2 (B), SW13.2 (B), SW14.2 (B), SW15.2 (B), SW16.2 (B), SW17.2 (B), SW18.2 (B), SW19.2 (B), SW20.2 (B), SW21.2 (B), SW22.2 (B), SW23.2 (B), SW24.2 (B), SW25.2 (B)
